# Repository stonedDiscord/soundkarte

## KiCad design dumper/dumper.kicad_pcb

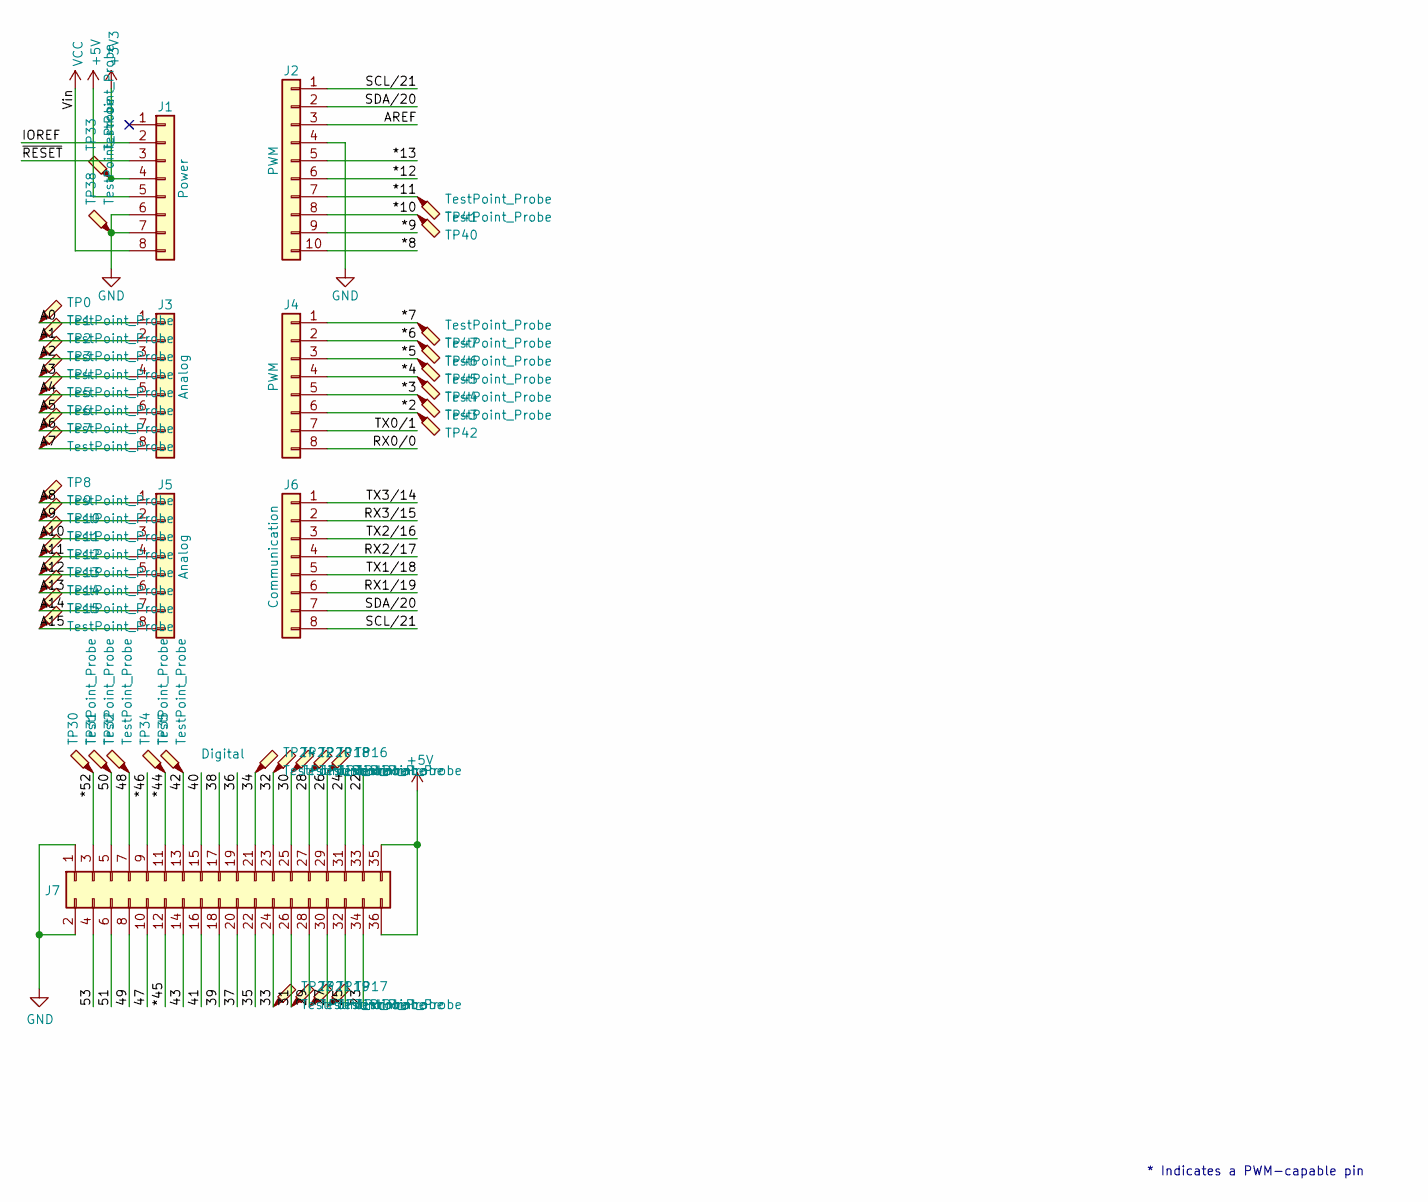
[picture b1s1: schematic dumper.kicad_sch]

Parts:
J1: Power; PinSocket_1x08_P2.54mm_Vertical
J2: PWM; PinSocket_1x10_P2.54mm_Vertical
J3, J5: Analog; PinSocket_1x08_P2.54mm_Vertical
J4: PWM; PinSocket_1x08_P2.54mm_Vertical
J6: Communication; PinSocket_1x08_P2.54mm_Vertical
J7: Digital; PinSocket_2x18_P2.54mm_Vertical
TP0, TP1, TP2, TP3, TP4, TP5, TP6, TP7, TP8, TP9, TP10, TP11, TP12, TP13, TP14, TP15, TP16, TP17, TP18, TP19, TP20, TP21, TP22, TP23, TP24, TP30, TP31, TP32, TP33, TP34, TP35, TP38, TP40, TP41, TP42, TP43, TP44, TP45, TP46, TP47: TestPoint_Probe; PinHeader_1x01_P1.00mm_Vertical

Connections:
+3V3: J1.4, TP33.1
+5V: J1.5, J7.35, J7.36
/22: J7.33
/23: J7.34
/24: J7.31
/25: J7.32
/26: J7.29, TP16.1
/27: J7.30, TP17.1
/28: J7.27, TP18.1
/29: J7.28, TP19.1
/30: J7.25, TP20.1
/31: J7.26, TP21.1
/32: J7.23, TP22.1
/33: J7.24, TP23.1
/34: J7.21, TP24.1
/35: J7.22
/36: J7.19
/37: J7.20
/38: J7.17
/39: J7.18
/40: J7.15
/41: J7.16
/42: J7.13, TP35.1
/43: J7.14
/47: J7.10
/48: J7.7, TP32.1
/49: J7.8
/50: J7.5, TP31.1
/51: J7.6
/53: J7.4
/*2: J4.6, TP42.1
/*3: J4.5, TP43.1
/*4: J4.4, TP44.1
/*5: J4.3, TP45.1
/*6: J4.2, TP46.1
/*7: J4.1, TP47.1
/*8: J2.10
/*9: J2.9
/*10: J2.8, TP40.1
/*11: J2.7, TP41.1
/*12: J2.6
/*13: J2.5
/*44: J7.11, TP34.1
/*45: J7.12
/*46: J7.9
/*52: J7.3, TP30.1
/A0: J3.1, TP0.1
/A1: J3.2, TP1.1
/A2: J3.3, TP2.1
/A3: J3.4, TP3.1
/A4: J3.5, TP4.1
/A5: J3.6, TP5.1
/A6: J3.7, TP6.1
/A7: J3.8, TP7.1
/A8: J5.1, TP8.1
/A9: J5.2, TP9.1
/A10: J5.3, TP10.1
/A11: J5.4, TP11.1
/A12: J5.5, TP12.1
/A13: J5.6, TP13.1
/A14: J5.7, TP14.1
/A15: J5.8, TP15.1
/AREF: J2.3
/IOREF: J1.2
/RX0/0: J4.8
/RX1/19: J6.6
/RX2/17: J6.4
/RX3/15: J6.2
/SCL/21: J2.1, J6.8
/SDA/20: J2.2, J6.7
/TX0/1: J4.7
/TX1/18: J6.5
/TX2/16: J6.3
/TX3/14: J6.1
/~RESET: J1.3
GND: J1.6, J1.7, J2.4, J7.1, J7.2, TP38.1
VCC: J1.8

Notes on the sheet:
* Indicates a PWM-capable pin

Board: 2 copper layers, 53 parts (0 on the bottom side), 43 nets, no tracks yet.

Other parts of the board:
MH1, MH2, MH3, MH4, MH5, MH6: MountingHole_3.2mm

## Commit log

2024-12-19 reset
2024-12-24 verbindungen
2025-02-06 testpunkte
2025-03-17 loeschen
2025-04-20 teensy
2025-04-20 unterseite
2025-04-20 jtag
2025-04-21 56pin sockel falls es geht geht es
2025-05-02 linguist override
2025-10-10 tsop
